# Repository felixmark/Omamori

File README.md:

# Omamori
Omamori is a solar-powered LED lucky and protector charm.<br>
I have got the motivation to realize this project during my time in university, when I first designed PCBs, even though I had the idea for much longer. At first, I was using Altium Designer, which was used by my university. Later since version 2.0 I switched to KiCad, which is a gem of software, which was recommended to me by Andreas.<br>
A huge thank you for helping me with soldering, designing, listening and keeping my motivation up to:<br>
Andreas, Markus, Patrick, Anna-Lena, Flopsi, Stephan and many others! ♥️<br>
<br>

## Programming

Program ATTiny 1626 via UPDI pins on the back of the PCB.  
Set the internal clock to 1MHz and use a low uploading BAUD to make sure the microcontroller can keep up.  

<br><br>

# History

A version History of the Omamori project.

[Version 0.3.1](#Version-030) \
[Version 0.3.0](#Version-030) \
[Version 0.2.1](#Version-021) \
[Version 0.2.0](#Version-020) \
[Version 0.1.0](#Version-010)
<br><br>

## Version 0.3.1

\
Hardware as in Version 0.3.0 except that a few capacitors are closer to the BQ25570 and I added a few other transistors for stability. Everything is working as expected.  
I consider this the final version for now.  

<br><br>

## Version 0.3.0

\
**MCU:** 1x ATTiny 1626 \
**Energy Harvester:** 1x BQ25570 \
**Solar Cells:** 2x KXOB25-05X3F \
**LEDS:** 3x Orange 0805 SMD LED

<br><br>

## Version 0.2.1

\
Hardware as in Version 0.2.0 except a few resistors instead of the diode for measuring battery voltage and an IRLML2502 N-Channel MOSFET for switching the 5V boost converter.
This version works, but has a very short supercap lifetime. Therefore the next version has to be a lot more efficient.

<br><br>

## Version 0.2.0

\
**MCU:** 1x ATTiny 85 \
**Energy Harvester:** 1x BQ25504 \
**Solar Cells:** 2x KXOB25-05X3F \
**Boost Converter:** 1x TPS61222 \
**LED:** 1x SK6812 programmable RGBW LED

### Energy Harvester (BQ25504) properties

```
V_REF_SAMP    = 3.33V (R_OC1 = 6.2 MOhm + 10 MOhm = 16.2 MOhm, R_OC2 = 3.9 MOhm)
V_BAT_UV      = 2.21V (R_UV1 = 5.6 MOhm, R_UV2 = 4.3MOhm)
V_BAT_OK      = 2.27V (R_OK1 = 3.3 MOhm, R_OK2 = 2.7 MOhm, R_OK3 = 3.3 MOhm)
V_BAT_OK_HYST = 3.52V
V_BAT_OV      = 5.42V (R_OV1 = 3.6 MOhm, R_OV2 = 6.8 MOhm)
```

<br><br>

## Version 0.1.0

\
**MCU:** 1x MSP430G2210 \
**Energy Harvester:** 1x LTC3105 \
**Solar Cells:** 2x KXOB22-04X3L 1.5Vmpp \
**LED:** 1x Natural White LED

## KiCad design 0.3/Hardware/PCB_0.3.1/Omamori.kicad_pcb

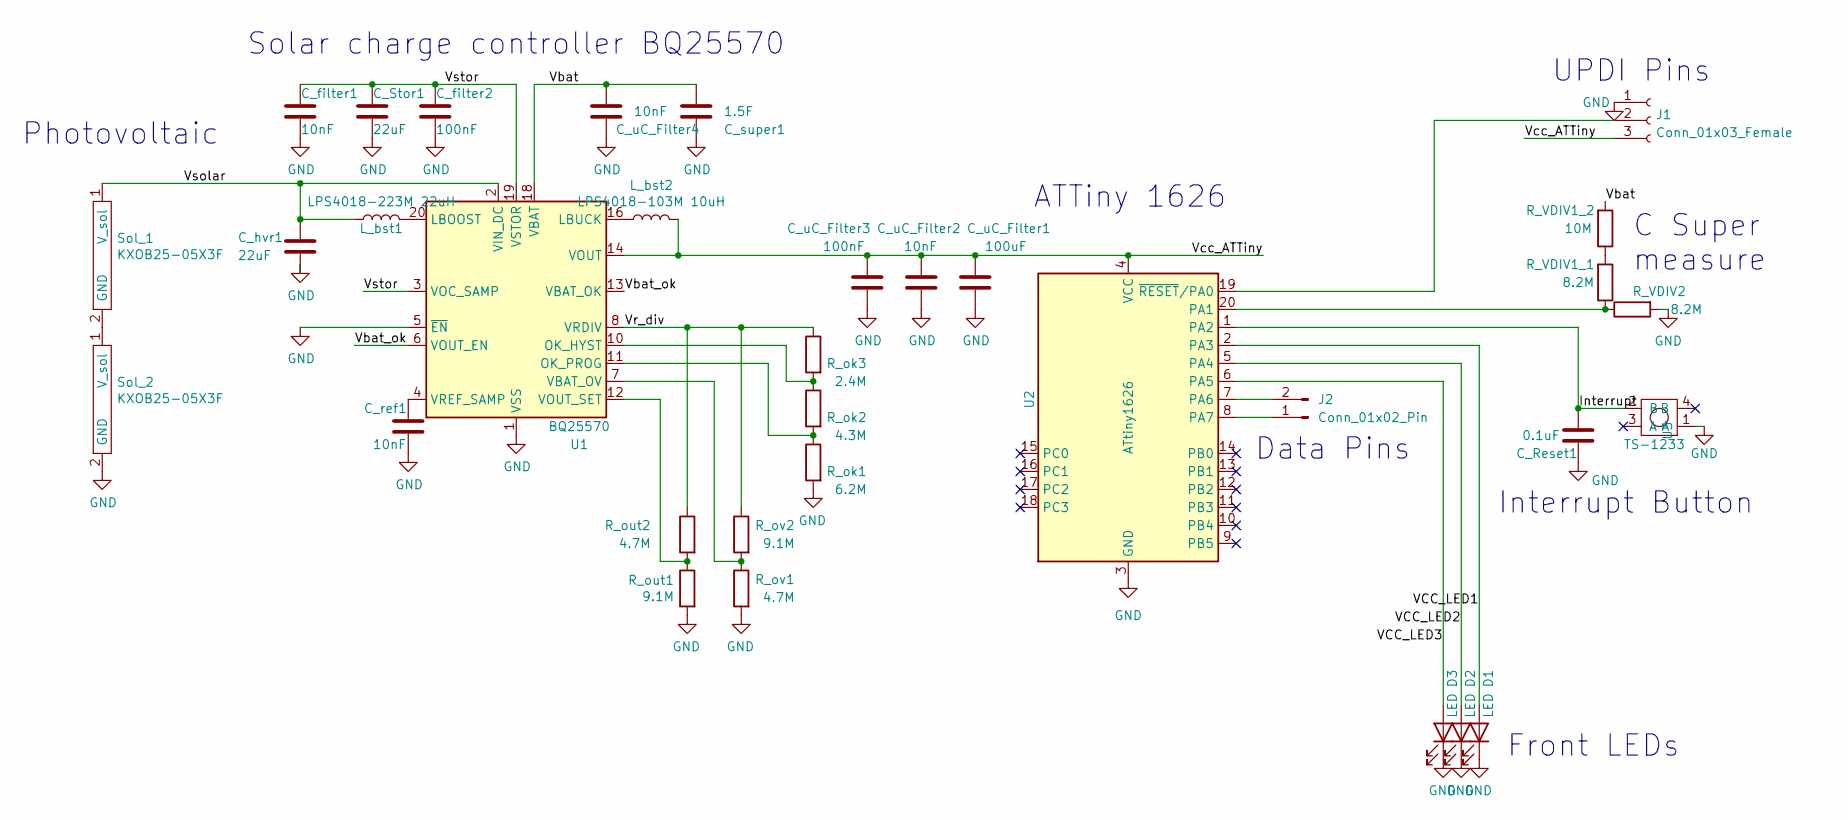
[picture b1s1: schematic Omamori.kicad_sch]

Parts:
C_Reset1: 0.1uF; C_0603_1608Metric_Pad1.08x0.95mm_HandSolder
C_Stor1: 22uF; C_0805_2012Metric_Pad1.18x1.45mm_HandSolder
C_filter1: 10nF; C_0603_1608Metric_Pad1.05x0.95mm_HandSolder
C_filter2: 100nF; C_0603_1608Metric_Pad1.08x0.95mm_HandSolder
C_hvr1: 22uF; C_0805_2012Metric_Pad1.18x1.45mm_HandSolder
C_ref1: 10nF; C_0603_1608Metric_Pad1.08x0.95mm_HandSolder
C_super1: 1.5F; Supercap_1F
C_uC_Filter1: 100uF; C_1206_3216Metric_Pad1.33x1.80mm_HandSolder
C_uC_Filter2, C_uC_Filter4: 10nF; C_0603_1608Metric_Pad1.08x0.95mm_HandSolder
C_uC_Filter3: 100nF; C_0603_1608Metric_Pad1.08x0.95mm_HandSolder
D1, D2, D3: LED; LED_0805_2012Metric
J1: Conn_01x03_Female; PinHeader_1x03_P2.54mm_Vertical
J2: Conn_01x02_Pin; PinHeader_1x02_P2.54mm_Vertical
L_bst1: LPS4018-223M 22uH; L_Coilcraft_LPS4018
L_bst2: LPS4018-103M 10uH; L_Coilcraft_LPS4018
R_VDIV1_1, R_VDIV2: 8.2M; R_0603_1608Metric_Pad0.98x0.95mm_HandSolder
R_VDIV1_2: 10M; R_0603_1608Metric_Pad0.98x0.95mm_HandSolder
R_ok1: 6.2M; R_0603_1608Metric_Pad1.05x0.95mm_HandSolder
R_ok2: 4.3M; R_0603_1608Metric_Pad1.05x0.95mm_HandSolder
R_ok3: 2.4M; R_0603_1608Metric_Pad1.05x0.95mm_HandSolder
R_out1: 9.1M; R_0603_1608Metric_Pad1.05x0.95mm_HandSolder
R_out2: 4.7M; R_0603_1608Metric_Pad1.05x0.95mm_HandSolder
R_ov1: 4.7M; R_0603_1608Metric_Pad1.05x0.95mm_HandSolder
R_ov2: 9.1M; R_0603_1608Metric_Pad1.05x0.95mm_HandSolder
Sol_1, Sol_2: KXOB25-05X3F
U1: BQ25570; QFN-20-1EP_3.5x3.5mm_P0.5mm_EP2x2mm
U2: ATtiny1626; VQFN-20-1EP_3x3mm_P0.4mm_EP1.7x1.7mm
U3: TS-1233

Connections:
/Interrupt: C_Reset1.2, U2.1 (PA2), U3.2 (B)
/VCC_LED1: D1.2 (A), U2.2 (PA3)
/VCC_LED2: D2.2 (A), U2.5 (PA4)
/VCC_LED3: D3.2 (A), U2.6 (PA5)
/Vbat: C_super1.2, C_uC_Filter4.1, R_VDIV1_2.2, U1.18 (VBAT)
/Vbat_ok: U1.6 (VOUT_EN), U1.13 (VBAT_OK)
/Vcc_ATTiny: C_uC_Filter1.1, C_uC_Filter2.1, C_uC_Filter3.1, J1.3, L_bst2.2, U1.14 (VOUT), U2.4 (VCC)
/Vr_div: R_ok3.1, R_out2.1, R_ov2.1, U1.8 (VRDIV)
/Vsolar: C_hvr1.1, L_bst1.1, Sol_1.1 (V_sol), U1.2 (VIN_DC)
/Vstor: C_Stor1.1, C_filter1.1, C_filter2.1, U1.3 (VOC_SAMP), U1.19 (VSTOR)
GND: C_Reset1.1, C_Stor1.2, C_filter1.2, C_filter2.2, C_hvr1.2, C_ref1.2, C_super1.1, C_uC_Filter1.2, C_uC_Filter2.2, C_uC_Filter3.2, C_uC_Filter4.2, D1.1 (K), D2.1 (K), D3.1 (K), J1.1, R_VDIV2.2, R_ok1.2, R_out1.2, R_ov1.2, Sol_2.2 (GND), U1.1 (VSS), U1.5 (~EN), U1.9 (VSS), U1.15 (VSS), U1.17 (VSS), U1.21 (VSS), U2.3 (GND), U2.21 (GND), U3.1 (A)
unnamed: J1.2, U2.19 (~RESET/PA0)
unnamed: J2.1, U2.8 (PA7)
unnamed: J2.2, U2.7 (PA6)
unnamed: R_VDIV1_1.2, R_VDIV1_2.1
unnamed: Sol_1.2 (GND), Sol_2.1 (V_sol)
unnamed: L_bst1.2, U1.20 (LBOOST)
unnamed: L_bst2.1, U1.16 (LBUCK)
unnamed: R_ok2.1, R_ok3.2, U1.10 (OK_HYST)
unnamed: R_ok1.1, R_ok2.2, U1.11 (OK_PROG)
unnamed: R_ov1.1, R_ov2.2, U1.7 (VBAT_OV)
unnamed: R_out1.1, R_out2.2, U1.12 (VOUT_SET)
unnamed: C_ref1.1, U1.4 (VREF_SAMP)
unnamed: R_VDIV1_1.1, R_VDIV2.1, U2.20 (PA1)

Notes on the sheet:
UPDI Pins
C Super measure
Front LEDs
Photovoltaic
Data Pins
Interrupt Button
Solar charge controller BQ25570
ATTiny 1626

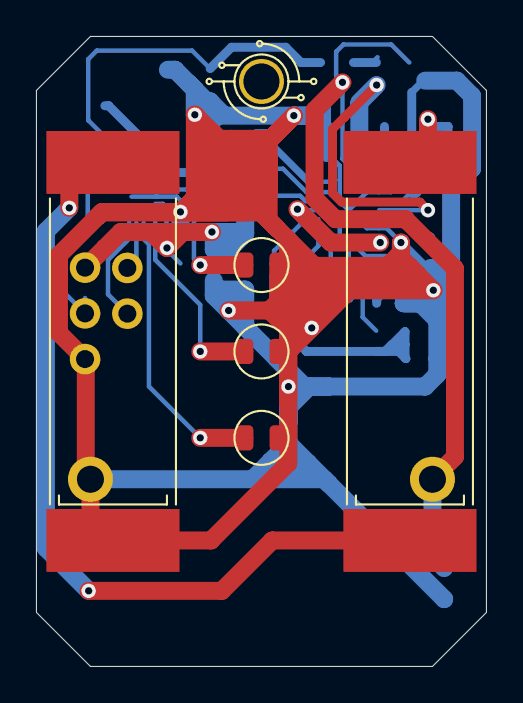
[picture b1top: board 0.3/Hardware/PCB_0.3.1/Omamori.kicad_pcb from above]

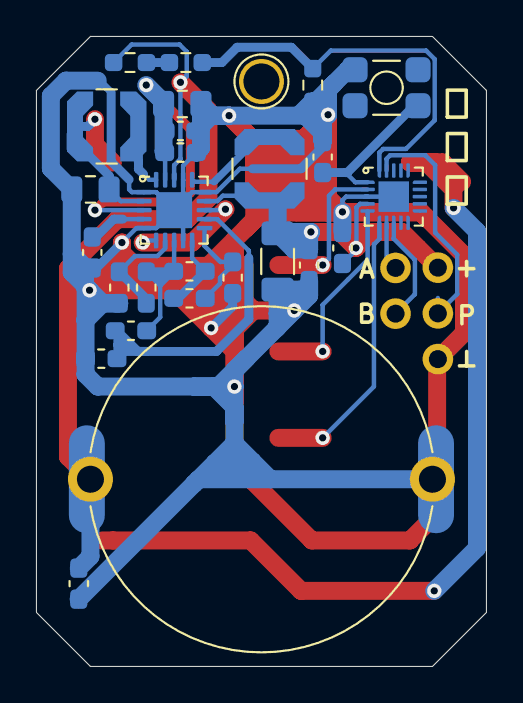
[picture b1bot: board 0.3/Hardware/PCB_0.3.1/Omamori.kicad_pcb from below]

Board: 2 copper layers, 25.0 x 35.0 mm, 33 parts (28 on the bottom side), 24 nets.

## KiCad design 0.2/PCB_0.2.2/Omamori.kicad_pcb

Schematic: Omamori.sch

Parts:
C_Stor1: 10uF; C_0805_2012Metric_Pad1.18x1.45mm_HandSolder
C_filter1: 0.1uF; C_0603_1608Metric_Pad1.05x0.95mm_HandSolder
C_hvr1: 4.7uF; C_0603_1608Metric_Pad1.05x0.95mm_HandSolder
C_led1: 100nF; C_0603_1608Metric_Pad1.05x0.95mm_HandSolder
C_post_boost1: 10uF; C_0805_2012Metric_Pad1.18x1.45mm_HandSolder
C_pre_boost1: 10uF; C_0805_2012Metric_Pad1.18x1.45mm_HandSolder
C_ref1: 0.01uF; C_0603_1608Metric_Pad1.05x0.95mm_HandSolder
C_super1: 640mF; Supercap
D1: SK6812; LED_SK6812_PLCC4_5.0x5.0mm_P3.2mm
J1: Conn_01x04_Female; PinHeader_1x04_P1.27mm_Horizontal
L_boost1: 4.7uH; L_Wuerth_MAPI-3015
L_bst1: 22uH; L_Wuerth_MAPI-3015
Q1: IRLML0030; SOT-23
R_data1: 500; R_0603_1608Metric_Pad1.05x0.95mm_HandSolder
R_oc1: 5.6M; R_0603_1608Metric_Pad0.98x0.95mm_HandSolder
R_oc1_2: 10M; R_0603_1608Metric_Pad1.05x0.95mm_HandSolder
R_oc2: 3.9M; R_0603_1608Metric_Pad1.05x0.95mm_HandSolder
R_ok1, R_ok3: 3.3M; R_0603_1608Metric_Pad1.05x0.95mm_HandSolder
R_ok2: 2.7M; R_0603_1608Metric_Pad1.05x0.95mm_HandSolder
R_ov1: 6.8M; R_0603_1608Metric_Pad1.05x0.95mm_HandSolder
R_ov2: 3.3M; R_0603_1608Metric_Pad1.05x0.95mm_HandSolder
R_pulldown1: 10M; R_0603_1608Metric_Pad1.05x0.95mm_HandSolder
R_uv1: 5.6M; R_0603_1608Metric_Pad1.05x0.95mm_HandSolder
R_uv2: 4.3M; R_0603_1608Metric_Pad1.05x0.95mm_HandSolder
R_vdiv_1: 1.8M; R_0603_1608Metric_Pad0.98x0.95mm_HandSolder
R_vdiv_2_1: 8.2M; R_0603_1608Metric_Pad0.98x0.95mm_HandSolder
R_vdiv_2_2: 10M; R_0603_1608Metric_Pad0.98x0.95mm_HandSolder
Sol_1, Sol_2: KXOB25-05X3F
U1: BQ25504; VQFN-16-1EP_3x3mm_P0.5mm_EP1.8x1.8mm
U2: TPS61222DCK; Texas_R-PDSO-G6
U3: ATtiny85; SOIC-8_5.275x5.275mm_P1.27mm
U4: TS-1233

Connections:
/Data_LED: R_data1.2, U3.3
/Din_LED: D1.2, R_data1.1
/Drain: C_led1.2, C_post_boost1.2, C_pre_boost1.2, D1.1, J1.4, Q1.3, R_vdiv_2_2.1, U2.3, U3.4, U4.3
/Reset: U3.1, U4.2
/Rx: J1.2, U3.6
/Tx: J1.3, U3.5
/Vbat: C_pre_boost1.1, C_super1.1, L_boost1.1, R_vdiv_1.1, U1.14, U2.1, U2.6
/Vbat_ok: Q1.1, R_pulldown1.2, U1.11
/Vcc_ATTiny: C_post_boost1.1, J1.1, U2.2, U2.4, U3.8
/Vcc_LED: C_led1.1, D1.3, U3.2
/Vmeasure: R_vdiv_1.2, R_vdiv_2_1.2, U3.7
/Vr_div: R_ok3.1, R_ov1.1, R_uv2.1, U1.7
/Vsolar: C_hvr1.1, L_bst1.1, R_oc2.1, Sol_1.1 (V_sol), U1.2
GND: C_Stor1.2, C_filter1.2, C_hvr1.2, C_ref1.2, C_super1.2, Q1.2, R_oc1_2.1, R_ok1.2, R_ov2.2, R_pulldown1.1, R_uv1.2, Sol_2.2 (GND), U1.1, U1.5, U1.12, U1.13, U1.17
unnamed: C_Stor1.1, C_filter1.1, U1.15
unnamed: C_ref1.1, U1.4
unnamed: L_boost1.2, U2.5
unnamed: L_bst1.2, U1.16
unnamed: R_oc1.1, R_oc1_2.2
unnamed: R_oc1.2, R_oc2.2, U1.3
unnamed: R_ok1.1, R_ok2.2, U1.10
unnamed: R_ok2.1, R_ok3.2, U1.9
unnamed: R_ov1.2, R_ov2.1, U1.6
unnamed: R_uv1.1, R_uv2.2, U1.8
unnamed: R_vdiv_2_1.1, R_vdiv_2_2.2
unnamed: Sol_1.2 (GND), Sol_2.1 (V_sol)

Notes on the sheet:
5V Boost Converter
Voltage Divider
Serial Pins
AT Tiny
RGBW LED
Solar charge controller
Photovoltaic

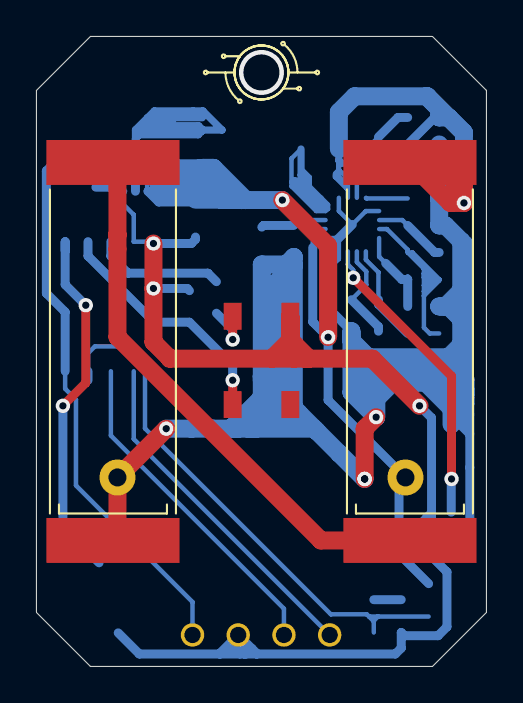
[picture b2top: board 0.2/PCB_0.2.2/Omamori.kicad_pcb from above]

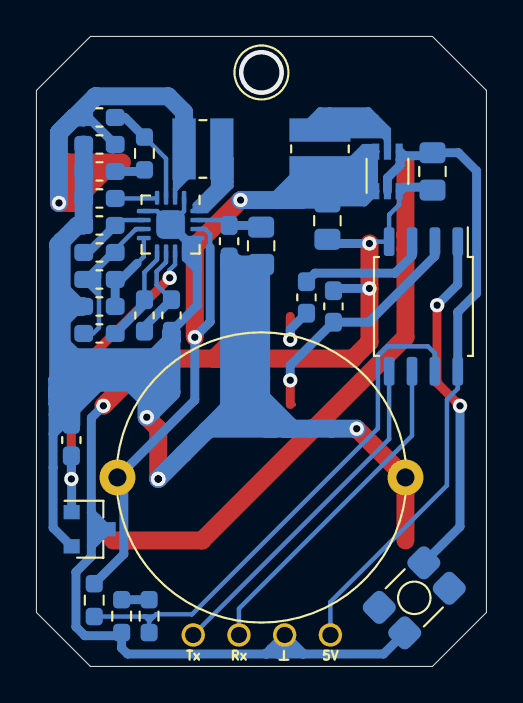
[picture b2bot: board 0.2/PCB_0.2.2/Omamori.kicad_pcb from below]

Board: 2 copper layers, 25.0 x 35.0 mm, 34 parts (31 on the bottom side), 26 nets.

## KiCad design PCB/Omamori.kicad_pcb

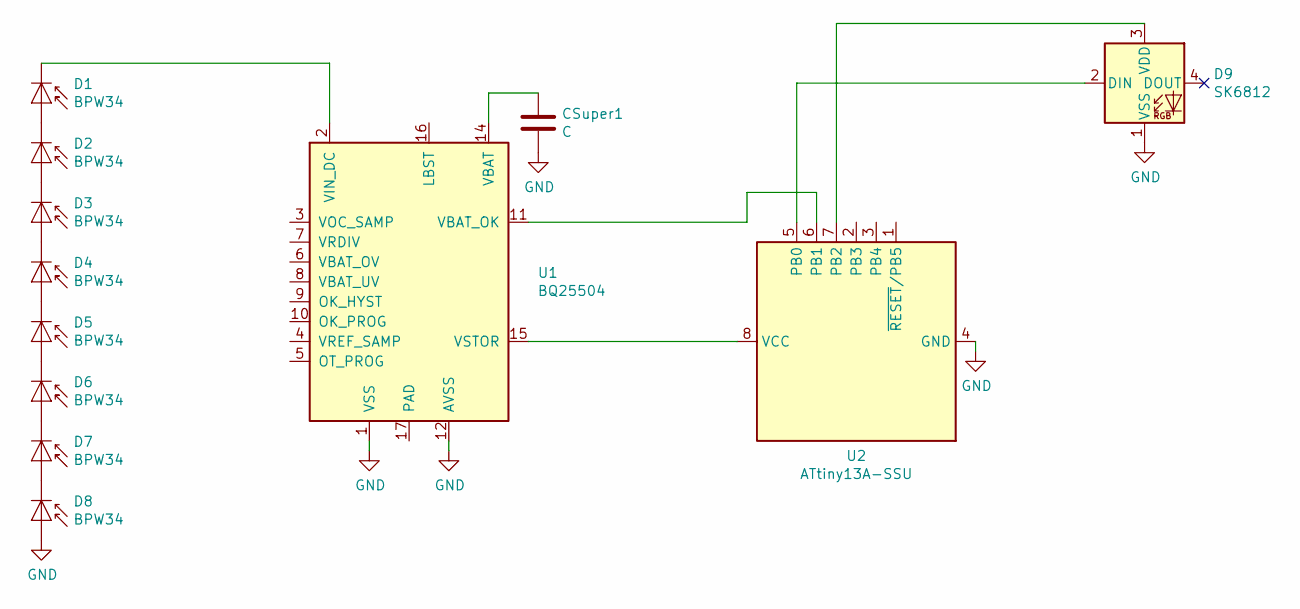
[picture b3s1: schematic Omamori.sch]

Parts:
CSuper1: C; C_Rect_L7.2mm_W2.5mm_P5.00mm_FKS2_FKP2_MKS2_MKP2
D1, D2, D3, D4, D5, D6, D7, D8: BPW34; Osram_DIL2_4.3x4.65mm_P5.08mm
D9: SK6812; LED_SK6812_PLCC4_5.0x5.0mm_P3.2mm
U1: BQ25504; VQFN-16-1EP_3x3mm_P0.5mm_EP1.8x1.8mm
U2: ATtiny13A-SSU; SOIC-8_3.9x4.9mm_P1.27mm

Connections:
GND: CSuper1.2, D8.2 (A), D9.1 (VSS), U1.1 (VSS), U1.12 (AVSS), U1.13 (VSS), U2.4 (GND)
unnamed: CSuper1.1, U1.14 (VBAT)
unnamed: D1.1 (K), U1.2 (VIN_DC)
unnamed: D1.2 (A), D2.1 (K)
unnamed: D2.2 (A), D3.1 (K)
unnamed: D3.2 (A), D4.1 (K)
unnamed: D4.2 (A), D5.1 (K)
unnamed: D5.2 (A), D6.1 (K)
unnamed: D6.2 (A), D7.1 (K)
unnamed: D7.2 (A), D8.1 (K)
unnamed: D9.2 (DIN), U2.5 (PB0)
unnamed: D9.3 (VDD), U2.7 (PB2)
unnamed: U1.11 (VBAT_OK), U2.6 (PB1)
unnamed: U1.15 (VSTOR), U2.8 (VCC)

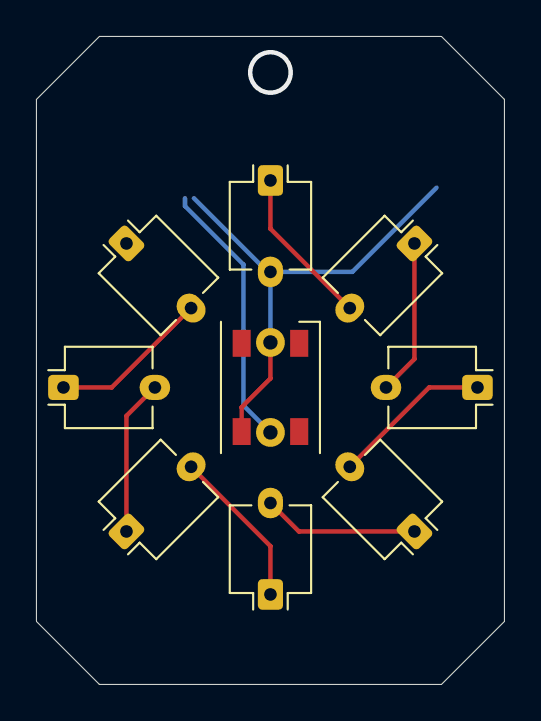
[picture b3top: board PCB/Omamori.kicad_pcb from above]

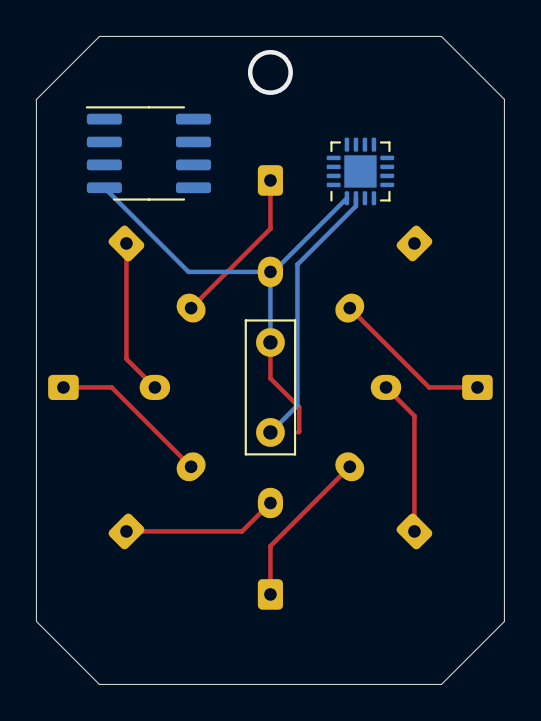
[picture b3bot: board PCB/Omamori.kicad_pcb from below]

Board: 2 copper layers, 26.0 x 36.0 mm, 12 parts (3 on the bottom side), 14 nets.

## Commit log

2021-03-15 Added current state of the PCB design.
2021-03-15 Made changes to PCB.
2021-03-15 Split project into v1 and v2 and added missing v2 files.
2021-03-15 Removed v1 Datasheets from Repository.
2021-03-15 Removed old Altium outputs.
2021-03-15 Removed all unnecessary Code Composer Project files.
2021-03-15 Updated Readme.
2021-03-15 Removed all unversioned files.
2021-03-20 Chenged Arduino program and added Datasheets and Pictures.
2021-03-26 Updated Arduino program, to detect voltage of solar panels.
2021-03-27 Added a crappy Schematic lol.
2021-04-01 Improved program with LED enable pin.
2021-04-09 Modified PCB and updated Software.
2021-04-30 Updated readme, schematic and the .ino program.
2021-04-30 Changed size of v1 PCB.
2021-05-16 Updated version 2 PCB.
2021-05-17 Updated PCB layout and added gerber and pictures.
2021-05-18 Thickened a lot of wires and ordered stuff a bit.
2021-05-18 Changed resistor position to make supercap fit.
2021-05-18 I am not sure what changed to be honest.
2021-05-18 Added a really ugly GND Polygon.
2021-05-20 Datasheet and description update as well as other minor design changes.
2021-05-24 Added reset button and changed a few wires.
2021-05-24 Updated program and modified PCB Layout to measure V_supercap.
2021-05-24 Updated Software a bit.
2021-05-25 Final version + gerber export.
2021-05-25 Beyond last second changes to the PCB design and gerber files.
2021-05-26 Changes made to Roc1 and Roc2.
2021-05-26 Did a bit of cleaning up and updated ATtiny program.
2021-06-01 Fixed endless communication problem.
2021-06-02 Fixed another endless communication problem.
2021-06-03 Fixed swapped resistor values.
2021-06-09 Fixed weird not working error.
2021-09-10 Complete overhaul of the project.
2021-10-28 Rename of folders.
2021-10-28 Removed weird backslash.
2021-12-18 Updated 0.2.1 PCB design.
2021-12-18 Updated Gerber zip.
2021-12-18 Updated readme and pictures.
2021-12-18 Updated images and added new solder guide.
2021-12-18 Updated pcb design and gerber files.
2021-12-18 Resized images.
2021-12-19 Updated Program and Readme.
2021-12-19 Moved stuff and changed Readme.
2021-12-19 Fixed linebreaks.
2021-12-20 Layout and Design redesign.
2021-12-20 Updated schematic image.
2021-12-21 Added pull down resistor.
2021-12-21 Minor Layout update.
2021-12-22 Final Version of v0.2 22.12.2021.
2021-12-22 Added Interactive BOM. Updated Gerber Files.
2021-12-22 I don't know what changed but okay.
2021-12-22 It's the last bom gerber export I plot today, I swear lol
2022-02-03 Updated ATTiny Program and wrote a serial communicator script for easier configuration.
2022-02-11 Created version 0.2.2 containing minor updates so far.
2022-02-11 Removed Bom from repo.
2022-02-11 Added new features to ATTiny program.
2022-02-11 Updated software for Omamori serial communication and modified sleeping settings.
2022-02-14 Changed serial communication to work on linux.
2022-02-15 Made Omamori programmer pretty and moved it.
2022-02-15 Checked for empty list.
2022-06-18 V3 update.
2022-06-18 V3 restructuring.
2022-06-18 Added version 3 to the readme.
2022-06-26 Unfinished update. Serial communication still unfinished.
2022-07-04 Voltage measurement update.
2022-07-05 Updated software to measure voltage.
2022-10-01 Updated hw.
2022-10-04 Moved some parts.
2022-10-05 Temporarily finished pcb design.
2022-10-07 Updated pcb.
2022-10-07 Removed backups and changed a trace thickness.
2022-10-07 Small redesign
2022-10-08 New v3 layout and image.
2022-10-08 Correct pcb design update for v3.
2022-10-08 Updated pcb image.
2022-10-09 Updated to version, which got ordered on jlcpcb.
2022-10-22 Updated software.
2022-10-24 Renamed software to firmware and updated Firmware of v3.
2022-11-01 It works! Just change 2 resistors.
2022-11-02 Updated Omamori firmware.
2022-11-10 Updated Firmware for 0.3
2022-11-10 Added HW version 0.3.1
2022-11-17 HW Update before going to germany.
2023-01-29 Added pictures and updated Readme. Firmware will eventually change in the future.
2023-01-29 Whoops, forgot to add Readme.
2023-01-29 Fixed typo.
2023-11-28 Changed v3 Firmware to use correct ADC resolution.
2023-11-30 Firmware now has a nice button press interrupt.
2023-11-30 Fixed voltage measurement with awesome measurements. High resistance leads to weird behaviour.
2023-12-17 Updated Omamori 0.3.1.
